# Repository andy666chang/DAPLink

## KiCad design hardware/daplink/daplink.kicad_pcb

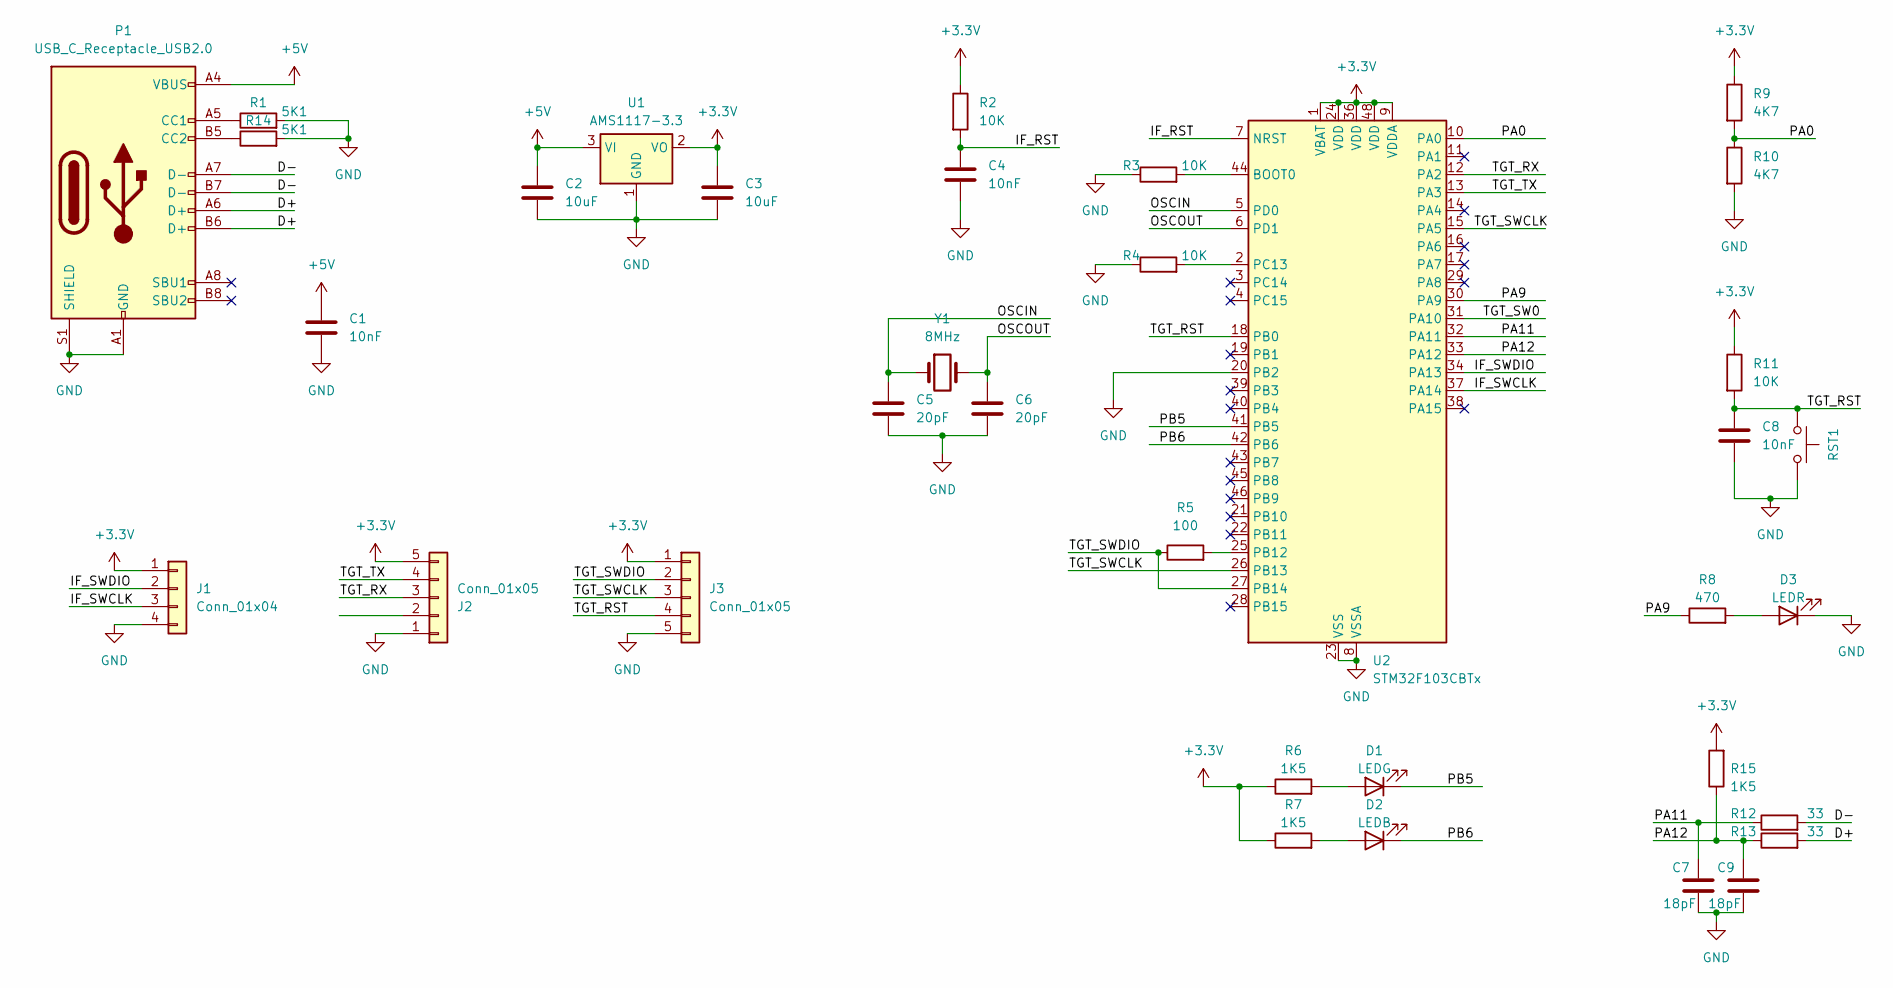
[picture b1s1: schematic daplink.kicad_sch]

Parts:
C1, C4, C8: 10nF; C_0603_1608Metric_Pad1.08x0.95mm_HandSolder; JLCPCB C57112
C2, C3: 10uF; C_0603_1608Metric_Pad1.08x0.95mm_HandSolder; JLCPCB C19702
C5, C6: 20pF; C_0603_1608Metric_Pad1.08x0.95mm_HandSolder; JLCPCB C1648
C7, C9: 18pF; C_0603_1608Metric_Pad1.08x0.95mm_HandSolder; JLCPCB C1647
D1: LEDG; LED_0603_1608Metric_Pad1.05x0.95mm_HandSolder; JLCPCB C72041
D2: LEDB; LED_0603_1608Metric_Pad1.05x0.95mm_HandSolder; JLCPCB C72043
D3: LEDR; LED_0603_1608Metric_Pad1.05x0.95mm_HandSolder; JLCPCB C2286
J1: Conn_01x04; PinHeader_1x04_P2.54mm_Vertical
J2, J3: Conn_01x05; Harwin_M20-89005xx_1x05_P2.54mm_Horizontal
P1: USB_C_Receptacle_USB2.0; USB_C_Receptacle_GCT_USB4105-xx-A_16P_TopMnt_Horizontal; JLCPCB C2927038/C2927029
R1, R14: 5K1; R_0603_1608Metric_Pad0.98x0.95mm_HandSolder; JLCPCB C25804
R2, R3, R4, R11: 10K; R_0603_1608Metric_Pad0.98x0.95mm_HandSolder; JLCPCB C25804
R5: 100; R_0603_1608Metric_Pad0.98x0.95mm_HandSolder; JLCPCB C23162
R6, R7, R15: 1K5; R_0603_1608Metric_Pad0.98x0.95mm_HandSolder; JLCPCB C22843
R8: 470; R_0603_1608Metric_Pad0.98x0.95mm_HandSolder; JLCPCB C23179
R9, R10: 4K7; R_0603_1608Metric_Pad0.98x0.95mm_HandSolder; JLCPCB C23162
R12, R13: 33; R_0603_1608Metric_Pad0.98x0.95mm_HandSolder; JLCPCB C23140
RST1: RST; SW_Push_SPST_NO_Alps_SKRK
U1: AMS1117-3.3; SOT-223-3_TabPin2; JLCPCB C6186
U2: STM32F103CBTx; LQFP-48_7x7mm_P0.5mm; JLCPCB C8304
Y1: 8MHz; Crystal_SMD_5032-2Pin_5.0x3.2mm; JLCPCB C115962

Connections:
+3.3V: C3.1, J1.1, J2.5, J3.1, R2.1, R6.1, R7.1, R9.1, R11.1, R15.2, U1.2 (VO), U2.1 (VBAT), U2.9 (VDDA), U2.24 (VDD), U2.36 (VDD), U2.48 (VDD)
+5V: C1.1, C2.1, P1.A4 (VBUS), P1.A9 (VBUS), P1.B4 (VBUS), P1.B9 (VBUS), U1.3 (VI)
/D+: P1.A6 (D+), P1.B6 (D+), R13.2
/D-: P1.A7 (D-), P1.B7 (D-), R12.2
/IF_RST: C4.1, R2.2, U2.7 (NRST)
/IF_SWCLK: J1.3, U2.37 (PA14)
/IF_SWDIO: J1.2, U2.34 (PA13)
/OSCIN: C5.1, U2.5 (PD0), Y1.1
/OSCOUT: C6.1, U2.6 (PD1), Y1.2
/PA0: R9.2, R10.1, U2.10 (PA0)
/PA9: R8.1, U2.30 (PA9)
/PA11: C7.1, R12.1, U2.32 (PA11)
/PA12: C9.1, R13.1, R15.1, U2.33 (PA12)
/PB5: D1.1 (K), U2.41 (PB5)
/PB6: D2.1 (K), U2.42 (PB6)
/TGT_RST: C8.1, J3.4, R11.2, RST1.1, U2.18 (PB0)
/TGT_RX: J2.3, U2.12 (PA2)
/TGT_SW0: U2.31 (PA10)
/TGT_SWCLK: J3.3, U2.15 (PA5), U2.26 (PB13)
/TGT_SWDIO: J3.2, R5.1, U2.27 (PB14)
/TGT_TX: J2.4, U2.13 (PA3)
GND: C1.2, C2.2, C3.2, C4.2, C5.2, C6.2, C7.2, C8.2, C9.2, D3.1 (K), J1.4, J2.1, J3.5, P1.A1 (GND), P1.A12 (GND), P1.B1 (GND), P1.B12 (GND), P1.S1 (SHIELD), R1.2, R3.1, R4.1, R10.2, R14.2, RST1.2, U1.1 (GND), U2.8 (VSSA), U2.20 (PB2), U2.23 (VSS), U2.35 (VSS), U2.47 (VSS)
unnamed: D1.2 (A), R6.2
unnamed: D2.2 (A), R7.2
unnamed: D3.2 (A), R8.2
unnamed: P1.A5 (CC1), R1.1
unnamed: P1.B5 (CC2), R14.1
unnamed: R3.2, U2.44 (BOOT0)
unnamed: R5.2, U2.25 (PB12)
unnamed: R4.2, U2.2 (PC13)

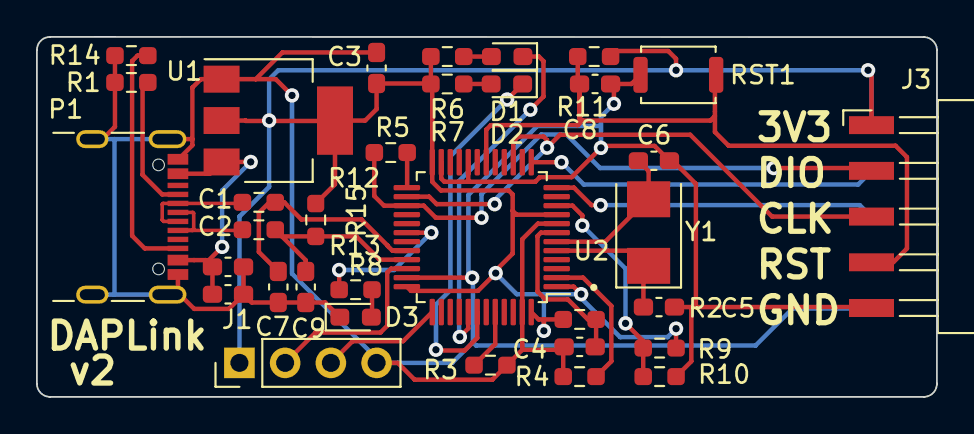
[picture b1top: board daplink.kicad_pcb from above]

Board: 2 copper layers, 50.0 x 20.0 mm, 35 parts (1 on the bottom side), 29 nets.

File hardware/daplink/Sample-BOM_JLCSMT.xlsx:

Comment | Designator | Footprint | JLCPCB Part #（optional）
10nF | C1 | Capacitor_SMD:C_0603_1608Metric_Pad1.08x0.95mm_HandSolder | C57112
10uF | C2 | Capacitor_SMD:C_0603_1608Metric_Pad1.08x0.95mm_HandSolder | C19702
10uF | C3 | Capacitor_SMD:C_0603_1608Metric_Pad1.08x0.95mm_HandSolder | C19702
10nF | C4 | Capacitor_SMD:C_0603_1608Metric_Pad1.08x0.95mm_HandSolder | C57112
20pF | C5 | Capacitor_SMD:C_0603_1608Metric_Pad1.08x0.95mm_HandSolder | C1648
20pF | C6 | Capacitor_SMD:C_0603_1608Metric_Pad1.08x0.95mm_HandSolder | C1648
18pF | C7 | Capacitor_SMD:C_0603_1608Metric_Pad1.08x0.95mm_HandSolder | C1647
10nF | C8 | Capacitor_SMD:C_0603_1608Metric_Pad1.08x0.95mm_HandSolder | C57112
18pF | C9 | Capacitor_SMD:C_0603_1608Metric_Pad1.08x0.95mm_HandSolder | C1647
LEDB | D1 | LED_SMD:LED_0603_1608Metric_Pad1.05x0.95mm_HandSolder | C72041
LEDG | D2 | LED_SMD:LED_0603_1608Metric_Pad1.05x0.95mm_HandSolder | C72043
LEDR | D3 | LED_SMD:LED_0603_1608Metric_Pad1.05x0.95mm_HandSolder | C2286
Conn_01x04 | J1 | Connector_PinHeader_2.54mm:PinHeader_1x04_P2.54mm_Vertical
Conn_01x05 | J2 | Connector_Harwin:Harwin_M20-89005xx_1x05_P2.54mm_Horizontal
Conn_01x05 | J3 | Connector_Harwin:Harwin_M20-89005xx_1x05_P2.54mm_Horizontal
USB_C_Plug_USB2.0 | P1 | Connector_USB:USB_C_Receptacle_GCT_USB4105-xx-A_16P_TopMnt_Horizontal | C2927038/C2927029
10K | R1 | Resistor_SMD:R_0603_1608Metric_Pad0.98x0.95mm_HandSolder | C25804
10K | R2 | Resistor_SMD:R_0603_1608Metric_Pad0.98x0.95mm_HandSolder | C25804
10K | R3 | Resistor_SMD:R_0603_1608Metric_Pad0.98x0.95mm_HandSolder | C25804
10K | R4 | Resistor_SMD:R_0603_1608Metric_Pad0.98x0.95mm_HandSolder | C25804
100 | R5 | Resistor_SMD:R_0603_1608Metric_Pad0.98x0.95mm_HandSolder | C22775
1K5 | R6 | Resistor_SMD:R_0603_1608Metric_Pad0.98x0.95mm_HandSolder | C22843
1K5 | R7 | Resistor_SMD:R_0603_1608Metric_Pad0.98x0.95mm_HandSolder | C22843
470 | R8 | Resistor_SMD:R_0603_1608Metric_Pad0.98x0.95mm_HandSolder | C23179
4K7 | R9 | Resistor_SMD:R_0603_1608Metric_Pad0.98x0.95mm_HandSolder | C23162
4K7 | R10 | Resistor_SMD:R_0603_1608Metric_Pad0.98x0.95mm_HandSolder | C23162
10K | R11 | Resistor_SMD:R_0603_1608Metric_Pad0.98x0.95mm_HandSolder | C25804
33 | R12 | Resistor_SMD:R_0603_1608Metric_Pad0.98x0.95mm_HandSolder | C23140
33 | R13 | Resistor_SMD:R_0603_1608Metric_Pad0.98x0.95mm_HandSolder | C23140
RST | RST1 | Button_Switch_SMD:SW_Push_SPST_NO_Alps_SKRK
AMS1117-3.3 | U1 | Package_TO_SOT_SMD:SOT-223-3_TabPin2 | C6186
STM32F103CBTx | U2 | Package_QFP:LQFP-48_7x7mm_P0.5mm | C8304
8MHz | Y1 | Crystal:Crystal_SMD_5032-2Pin_5.0x3.2mm | C115962

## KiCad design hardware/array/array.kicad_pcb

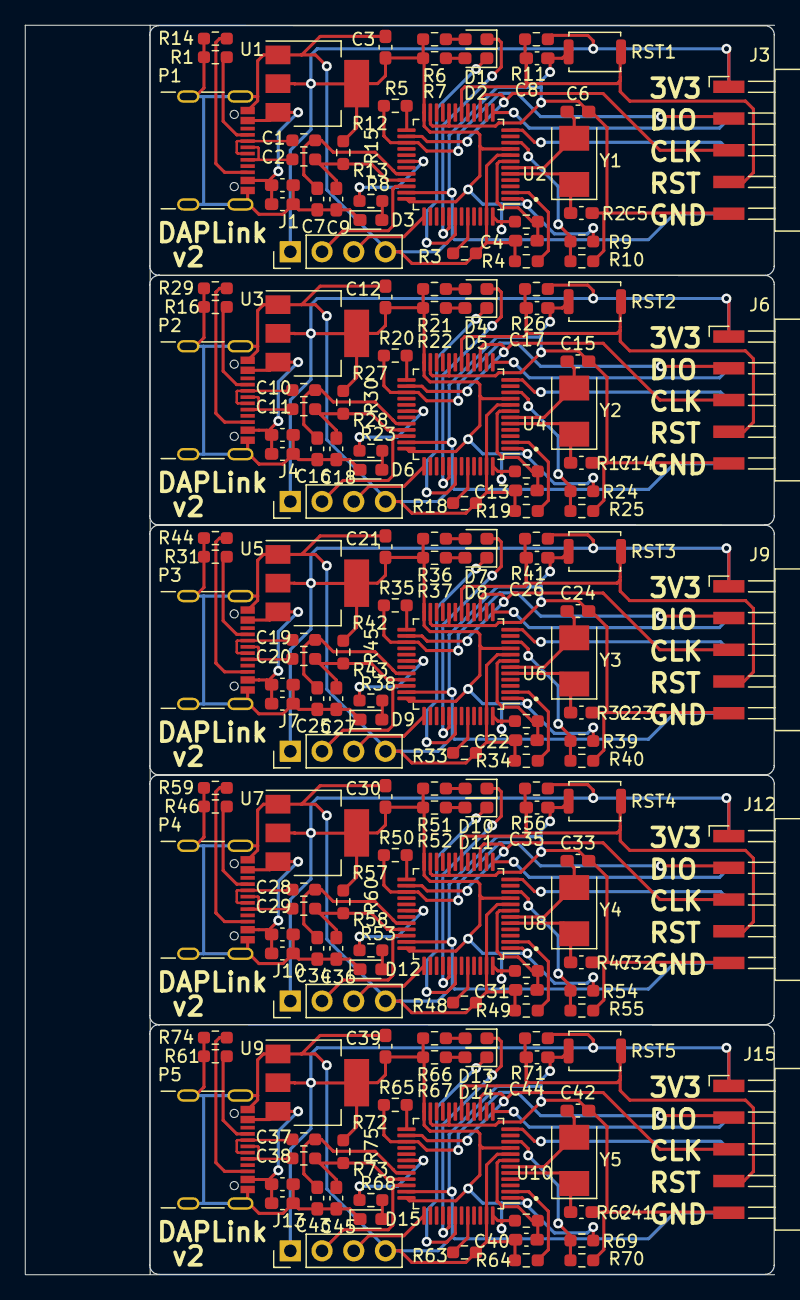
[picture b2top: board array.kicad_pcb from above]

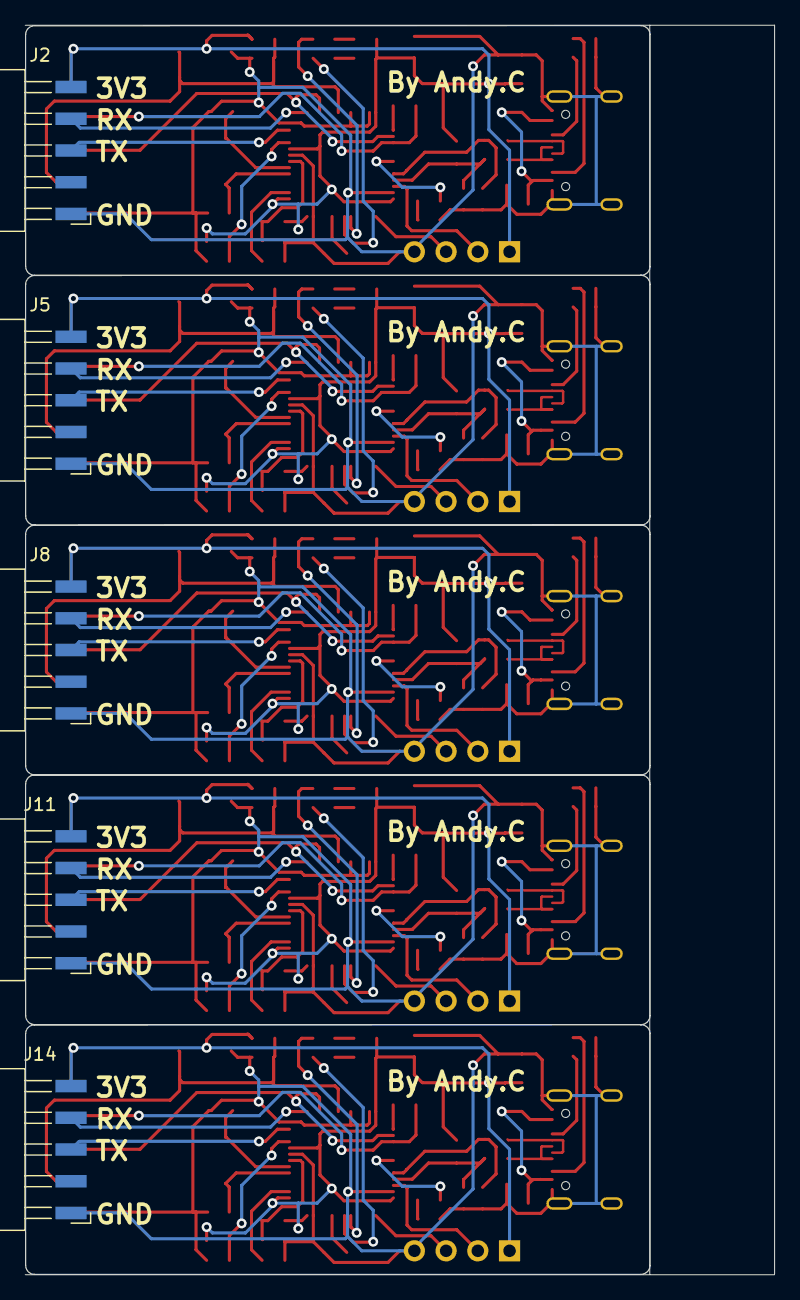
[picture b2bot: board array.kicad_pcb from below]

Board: 2 copper layers, 60.0 x 100.0 mm, 175 parts (5 on the bottom side), 30 nets.

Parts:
C1, C4, C8, C10, C13, C17, C19, C22, C26, C28, C31, C35, C37, C40, C44: 10nF; C_0603_1608Metric_Pad1.08x0.95mm_HandSolder
C2, C3, C11, C12, C20, C21, C29, C30, C38, C39: 10uF; C_0603_1608Metric_Pad1.08x0.95mm_HandSolder
C5, C6, C14, C15, C23, C24, C32, C33, C41, C42: 20pF; C_0603_1608Metric_Pad1.08x0.95mm_HandSolder
C7, C9, C16, C18, C25, C27, C34, C36, C43, C45: 18pF; C_0603_1608Metric_Pad1.08x0.95mm_HandSolder
D1, D4, D7, D10, D13: LEDG; LED_0603_1608Metric_Pad1.05x0.95mm_HandSolder
D2, D5, D8, D11, D14: LEDB; LED_0603_1608Metric_Pad1.05x0.95mm_HandSolder
D3, D6, D9, D12, D15: LEDR; LED_0603_1608Metric_Pad1.05x0.95mm_HandSolder
J1, J4, J7, J10, J13: Conn_01x04; PinHeader_1x04_P2.54mm_Vertical
J2, J3, J5, J6, J8, J9, J11, J12, J14, J15: Conn_01x05; Harwin_M20-89005xx_1x05_P2.54mm_Horizontal
P1, P2, P3, P4, P5: USB_C_Receptacle_USB2.0; USB_C_Receptacle_GCT_USB4105-xx-A_16P_TopMnt_Horizontal
R1, R14, R16, R29, R31, R44, R46, R59, R61, R74: 5K1; R_0603_1608Metric_Pad0.98x0.95mm_HandSolder
R2, R3, R4, R11, R17, R18, R19, R26, R32, R33, R34, R41, R47, R48, R49, R56, R62, R63, R64, R71: 10K; R_0603_1608Metric_Pad0.98x0.95mm_HandSolder
R5, R20, R35, R50, R65: 100; R_0603_1608Metric_Pad0.98x0.95mm_HandSolder
R6, R7, R15, R21, R22, R30, R36, R37, R45, R51, R52, R60, R66, R67, R75: 1K5; R_0603_1608Metric_Pad0.98x0.95mm_HandSolder
R8, R23, R38, R53, R68: 470; R_0603_1608Metric_Pad0.98x0.95mm_HandSolder
R9, R10, R24, R25, R39, R40, R54, R55, R69, R70: 4K7; R_0603_1608Metric_Pad0.98x0.95mm_HandSolder
R12, R13, R27, R28, R42, R43, R57, R58, R72, R73: 33; R_0603_1608Metric_Pad0.98x0.95mm_HandSolder
RST1, RST2, RST3, RST4, RST5: RST; SW_Push_SPST_NO_Alps_SKRK
U1, U3, U5, U7, U9: AMS1117-3.3; SOT-223-3_TabPin2
U2, U4, U6, U8, U10: STM32F103CBTx; LQFP-48_7x7mm_P0.5mm
Y1, Y2, Y3, Y4, Y5: 8MHz; Crystal_SMD_5032-2Pin_5.0x3.2mm

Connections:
+3.3V: C3.1, C12.1, C21.1, C30.1, C39.1, J1.1, J2.5, J3.1, J4.1, J5.5, J6.1, J7.1, J8.5, J9.1, J10.1, J11.5, J12.1, J13.1, J14.5, J15.1, R2.1, R6.1, R7.1, R9.1, R11.1, R15.2, R17.1, R21.1, R22.1, R24.1, R26.1, R30.2, R32.1, R36.1, R37.1, R39.1, R41.1, R45.2, R47.1, R51.1, R52.1, R54.1, R56.1, R60.2, R62.1, R66.1, R67.1, R69.1, R71.1, R75.2, U1.2 (VO), U2.1 (VBAT), U2.9 (VDDA), U2.24 (VDD), U2.36 (VDD), U2.48 (VDD), U3.2 (VO), U4.1 (VBAT), U4.9 (VDDA), U4.24 (VDD), U4.36 (VDD), U4.48 (VDD), U5.2 (VO), U6.1 (VBAT), U6.9 (VDDA), U6.24 (VDD), U6.36 (VDD), U6.48 (VDD), U7.2 (VO), U8.1 (VBAT), U8.9 (VDDA), U8.24 (VDD), U8.36 (VDD), U8.48 (VDD), U9.2 (VO), U10.1 (VBAT), U10.9 (VDDA), U10.24 (VDD), U10.36 (VDD), U10.48 (VDD)
+5V: C1.1, C2.1, C10.1, C11.1, C19.1, C20.1, C28.1, C29.1, C37.1, C38.1, P1.A4 (VBUS), P1.A9 (VBUS), P1.B4 (VBUS), P1.B9 (VBUS), P2.A4 (VBUS), P2.A9 (VBUS), P2.B4 (VBUS), P2.B9 (VBUS), P3.A4 (VBUS), P3.A9 (VBUS), P3.B4 (VBUS), P3.B9 (VBUS), P4.A4 (VBUS), P4.A9 (VBUS), P4.B4 (VBUS), P4.B9 (VBUS), P5.A4 (VBUS), P5.A9 (VBUS), P5.B4 (VBUS), P5.B9 (VBUS), U1.3 (VI), U3.3 (VI), U5.3 (VI), U7.3 (VI), U9.3 (VI)
/D+: P1.A6 (D+), P1.B6 (D+), P2.A6 (D+), P2.B6 (D+), P3.A6 (D+), P3.B6 (D+), P4.A6 (D+), P4.B6 (D+), P5.A6 (D+), P5.B6 (D+), R13.2, R28.2, R43.2, R58.2, R73.2
/D-: P1.A7 (D-), P1.B7 (D-), P2.A7 (D-), P2.B7 (D-), P3.A7 (D-), P3.B7 (D-), P4.A7 (D-), P4.B7 (D-), P5.A7 (D-), P5.B7 (D-), R12.2, R27.2, R42.2, R57.2, R72.2
/IF_RST: C4.1, C13.1, C22.1, C31.1, C40.1, R2.2, R17.2, R32.2, R47.2, R62.2, U2.7 (NRST), U4.7 (NRST), U6.7 (NRST), U8.7 (NRST), U10.7 (NRST)
/IF_SWCLK: J1.3, J4.3, J7.3, J10.3, J13.3, U2.37 (PA14), U4.37 (PA14), U6.37 (PA14), U8.37 (PA14), U10.37 (PA14)
/IF_SWDIO: J1.2, J4.2, J7.2, J10.2, J13.2, U2.34 (PA13), U4.34 (PA13), U6.34 (PA13), U8.34 (PA13), U10.34 (PA13)
/OSCIN: C5.1, C14.1, C23.1, C32.1, C41.1, U2.5 (PD0), U4.5 (PD0), U6.5 (PD0), U8.5 (PD0), U10.5 (PD0), Y1.1, Y2.1, Y3.1, Y4.1, Y5.1
/OSCOUT: C6.1, C15.1, C24.1, C33.1, C42.1, U2.6 (PD1), U4.6 (PD1), U6.6 (PD1), U8.6 (PD1), U10.6 (PD1), Y1.2, Y2.2, Y3.2, Y4.2, Y5.2
/PA0: R9.2, R10.1, R24.2, R25.1, R39.2, R40.1, R54.2, R55.1, R69.2, R70.1, U2.10 (PA0), U4.10 (PA0), U6.10 (PA0), U8.10 (PA0), U10.10 (PA0)
/PA9: R8.1, R23.1, R38.1, R53.1, R68.1, U2.30 (PA9), U4.30 (PA9), U6.30 (PA9), U8.30 (PA9), U10.30 (PA9)
/PA11: C7.1, C16.1, C25.1, C34.1, C43.1, R12.1, R27.1, R42.1, R57.1, R72.1, U2.32 (PA11), U4.32 (PA11), U6.32 (PA11), U8.32 (PA11), U10.32 (PA11)
/PA12: C9.1, C18.1, C27.1, C36.1, C45.1, R13.1, R15.1, R28.1, R30.1, R43.1, R45.1, R58.1, R60.1, R73.1, R75.1, U2.33 (PA12), U4.33 (PA12), U6.33 (PA12), U8.33 (PA12), U10.33 (PA12)
/PB5: D1.1 (K), D4.1 (K), D7.1 (K), D10.1 (K), D13.1 (K), U2.41 (PB5), U4.41 (PB5), U6.41 (PB5), U8.41 (PB5), U10.41 (PB5)
/PB6: D2.1 (K), D5.1 (K), D8.1 (K), D11.1 (K), D14.1 (K), U2.42 (PB6), U4.42 (PB6), U6.42 (PB6), U8.42 (PB6), U10.42 (PB6)
/TGT_RST: C8.1, C17.1, C26.1, C35.1, C44.1, J3.4, J6.4, J9.4, J12.4, J15.4, R11.2, R26.2, R41.2, R56.2, R71.2, RST1.1, RST2.1, RST3.1, RST4.1, RST5.1, U2.18 (PB0), U4.18 (PB0), U6.18 (PB0), U8.18 (PB0), U10.18 (PB0)
/TGT_RX: J2.3, J5.3, J8.3, J11.3, J14.3, U2.12 (PA2), U4.12 (PA2), U6.12 (PA2), U8.12 (PA2), U10.12 (PA2)
/TGT_SW0: U2.31 (PA10), U4.31 (PA10), U6.31 (PA10), U8.31 (PA10), U10.31 (PA10)
/TGT_SWCLK: J3.3, J6.3, J9.3, J12.3, J15.3, U2.15 (PA5), U2.26 (PB13), U4.15 (PA5), U4.26 (PB13), U6.15 (PA5), U6.26 (PB13), U8.15 (PA5), U8.26 (PB13), U10.15 (PA5), U10.26 (PB13)
/TGT_SWDIO: J3.2, J6.2, J9.2, J12.2, J15.2, R5.1, R20.1, R35.1, R50.1, R65.1, U2.27 (PB14), U4.27 (PB14), U6.27 (PB14), U8.27 (PB14), U10.27 (PB14)
/TGT_TX: J2.4, J5.4, J8.4, J11.4, J14.4, U2.13 (PA3), U4.13 (PA3), U6.13 (PA3), U8.13 (PA3), U10.13 (PA3)
GND: C1.2, C2.2, C3.2, C4.2, C5.2, C6.2, C7.2, C8.2, C9.2, C10.2, C11.2, C12.2, C13.2, C14.2, C15.2, C16.2, C17.2, C18.2, C19.2, C20.2, C21.2, C22.2, C23.2, C24.2, C25.2, C26.2, C27.2, C28.2, C29.2, C30.2, C31.2, C32.2, C33.2, C34.2, C35.2, C36.2, C37.2, C38.2, C39.2, C40.2, C41.2, C42.2, C43.2, C44.2, C45.2, D3.1 (K), D6.1 (K), D9.1 (K), D12.1 (K), D15.1 (K), J1.4, J2.1, J3.5, J4.4, J5.1, J6.5, J7.4, J8.1, J9.5, J10.4, J11.1, J12.5, J13.4, J14.1, J15.5, P1.A1 (GND), P1.A12 (GND), P1.B1 (GND), P1.B12 (GND), P1.S1 (SHIELD), P2.A1 (GND), P2.A12 (GND), P2.B1 (GND), P2.B12 (GND), P2.S1 (SHIELD), P3.A1 (GND), P3.A12 (GND), P3.B1 (GND), P3.B12 (GND), P3.S1 (SHIELD), P4.A1 (GND), P4.A12 (GND), P4.B1 (GND), P4.B12 (GND), P4.S1 (SHIELD), P5.A1 (GND), P5.A12 (GND), P5.B1 (GND), P5.B12 (GND), P5.S1 (SHIELD), R1.2, R3.1, R4.1, R10.2, R14.2, R16.2, R18.1, R19.1, R25.2, R29.2, R31.2, R33.1, R34.1, R40.2, R44.2, R46.2, R48.1, R49.1, R55.2, R59.2, R61.2, R63.1, R64.1, R70.2, R74.2, RST1.2, RST2.2, RST3.2, RST4.2, RST5.2, U1.1 (GND), U2.8 (VSSA), U2.20 (PB2), U2.23 (VSS), U2.35 (VSS), U2.47 (VSS), U3.1 (GND), U4.8 (VSSA), U4.20 (PB2), U4.23 (VSS), U4.35 (VSS), U4.47 (VSS), U5.1 (GND), U6.8 (VSSA), U6.20 (PB2), U6.23 (VSS), U6.35 (VSS), U6.47 (VSS), U7.1 (GND), U8.8 (VSSA), U8.20 (PB2), U8.23 (VSS), U8.35 (VSS), U8.47 (VSS), U9.1 (GND), U10.8 (VSSA), U10.20 (PB2), U10.23 (VSS), U10.35 (VSS), U10.47 (VSS)
unnamed: D1.2 (A), D4.2 (A), D7.2 (A), D10.2 (A), D13.2 (A), R6.2, R21.2, R36.2, R51.2, R66.2
unnamed: D2.2 (A), D5.2 (A), D8.2 (A), D11.2 (A), D14.2 (A), R7.2, R22.2, R37.2, R52.2, R67.2
unnamed: D3.2 (A), D6.2 (A), D9.2 (A), D12.2 (A), D15.2 (A), R8.2, R23.2, R38.2, R53.2, R68.2
unnamed: P1.A5 (CC1), P2.A5 (CC1), P3.A5 (CC1), P4.A5 (CC1), P5.A5 (CC1), R1.1, R16.1, R31.1, R46.1, R61.1
unnamed: P1.B5 (CC2), P2.B5 (CC2), P3.B5 (CC2), P4.B5 (CC2), P5.B5 (CC2), R14.1, R29.1, R44.1, R59.1, R74.1
unnamed: R3.2, R18.2, R33.2, R48.2, R63.2, U2.44 (BOOT0), U4.44 (BOOT0), U6.44 (BOOT0), U8.44 (BOOT0), U10.44 (BOOT0)
unnamed: R5.2, R20.2, R35.2, R50.2, R65.2, U2.25 (PB12), U4.25 (PB12), U6.25 (PB12), U8.25 (PB12), U10.25 (PB12)
unnamed: R4.2, R19.2, R34.2, R49.2, R64.2, U2.2 (PC13), U4.2 (PC13), U6.2 (PC13), U8.2 (PC13), U10.2 (PC13)

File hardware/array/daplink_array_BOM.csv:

"Reference","Value","Footprint","Datasheet","JLCPCB","數量"
"C1","10nF","Capacitor_SMD:C_0603_1608Metric_Pad1.08x0.95mm_HandSolder","~","C57112","1"
"C2","10uF","Capacitor_SMD:C_0603_1608Metric_Pad1.08x0.95mm_HandSolder","~","C19702","1"
"C3","10uF","Capacitor_SMD:C_0603_1608Metric_Pad1.08x0.95mm_HandSolder","~","C19702","1"
"C4","10nF","Capacitor_SMD:C_0603_1608Metric_Pad1.08x0.95mm_HandSolder","~","C57112","1"
"C5","20pF","Capacitor_SMD:C_0603_1608Metric_Pad1.08x0.95mm_HandSolder","~","C1648","1"
"C6","20pF","Capacitor_SMD:C_0603_1608Metric_Pad1.08x0.95mm_HandSolder","~","C1648","1"
"C7","18pF","Capacitor_SMD:C_0603_1608Metric_Pad1.08x0.95mm_HandSolder","~","C1647","1"
"C8","10nF","Capacitor_SMD:C_0603_1608Metric_Pad1.08x0.95mm_HandSolder","~","C57112","1"
"C9","18pF","Capacitor_SMD:C_0603_1608Metric_Pad1.08x0.95mm_HandSolder","~","C1647","1"
"D1","LEDG","LED_SMD:LED_0603_1608Metric_Pad1.05x0.95mm_HandSolder","~","C72041","1"
"D2","LEDB","LED_SMD:LED_0603_1608Metric_Pad1.05x0.95mm_HandSolder","~","C72043","1"
"D3","LEDR","LED_SMD:LED_0603_1608Metric_Pad1.05x0.95mm_HandSolder","~","C2286","1"
"J1","Conn_01x04","Connector_PinHeader_2.54mm:PinHeader_1x04_P2.54mm_Vertical","~","","1"
"J2","Conn_01x05","Connector_Harwin:Harwin_M20-89005xx_1x05_P2.54mm_Horizontal","~","","1"
"J3","Conn_01x05","Connector_Harwin:Harwin_M20-89005xx_1x05_P2.54mm_Horizontal","~","","1"
"P1","USB_C_Receptacle_USB2.0","Connector_USB:USB_C_Receptacle_GCT_USB4105-xx-A_16P_TopMnt_Horizontal","https://www.usb.org/sites/default/files/documents/usb_type-c.zip","C2927038/C2927029","1"
"R1","5K1","Resistor_SMD:R_0603_1608Metric_Pad0.98x0.95mm_HandSolder","~","C23186","1"
"R2","10K","Resistor_SMD:R_0603_1608Metric_Pad0.98x0.95mm_HandSolder","~","C25804","1"
"R3","10K","Resistor_SMD:R_0603_1608Metric_Pad0.98x0.95mm_HandSolder","~","C25804","1"
"R4","10K","Resistor_SMD:R_0603_1608Metric_Pad0.98x0.95mm_HandSolder","~","C25804","1"
"R5","100","Resistor_SMD:R_0603_1608Metric_Pad0.98x0.95mm_HandSolder","~","C22775","1"
"R6","1K5","Resistor_SMD:R_0603_1608Metric_Pad0.98x0.95mm_HandSolder","~","C22843","1"
"R7","1K5","Resistor_SMD:R_0603_1608Metric_Pad0.98x0.95mm_HandSolder","~","C22843","1"
"R8","470","Resistor_SMD:R_0603_1608Metric_Pad0.98x0.95mm_HandSolder","~","C23179","1"
"R9","4K7","Resistor_SMD:R_0603_1608Metric_Pad0.98x0.95mm_HandSolder","~","C23162","1"
"R10","4K7","Resistor_SMD:R_0603_1608Metric_Pad0.98x0.95mm_HandSolder","~","C23162","1"
"R11","10K","Resistor_SMD:R_0603_1608Metric_Pad0.98x0.95mm_HandSolder","~","C25804","1"
"R12","33","Resistor_SMD:R_0603_1608Metric_Pad0.98x0.95mm_HandSolder","~","C23140","1"
"R13","33","Resistor_SMD:R_0603_1608Metric_Pad0.98x0.95mm_HandSolder","~","C23140","1"
"R14","5K1","Resistor_SMD:R_0603_1608Metric_Pad0.98x0.95mm_HandSolder","~","C23186","1"
"R15","1K5","Resistor_SMD:R_0603_1608Metric_Pad0.98x0.95mm_HandSolder","~","C22843","1"
"RST1","RST","Button_Switch_SMD:SW_Push_SPST_NO_Alps_SKRK","~","","1"
"U1","AMS1117-3.3","Package_TO_SOT_SMD:SOT-223-3_TabPin2","http://www.advanced-monolithic.com/pdf/ds1117.pdf","C6186","1"
"U2","STM32F103CBTx","Package_QFP:LQFP-48_7x7mm_P0.5mm","https://www.st.com/resource/en/datasheet/stm32f103cb.pdf","C8304","1"
"Y1","8MHz","Crystal:Crystal_SMD_5032-2Pin_5.0x3.2mm","~","C115962","1"

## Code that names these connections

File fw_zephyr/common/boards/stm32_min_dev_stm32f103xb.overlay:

/*
 * DAPLink HIC (hardware/daplink) on stm32_min_dev (blue), STM32F103CB
 *
 * Shared by app (interface) and bootloader.
 *
 * Pin map follows DAPLink source/hic_hal/stm32/stm32f103xb/IO_Config.h
 * and hardware/daplink/daplink.kicad_sch:
 *   PB13  TGT_SWCLK
 *   PB14  TGT_SWDIO (out)
 *   PB12  TGT_SWDIO (in, via 4K7)
 *   PB0   TGT_RST   (open drain)
 *   PA2   TGT_RX    (USART2 TX -> target RX)
 *   PA3   TGT_TX    (USART2 RX <- target TX)
 *   PA10  TGT_SWO   (USART1 RX, SWO UART capture)
 *   PB6   LED blue  (active low)  - IF: connected
 *   PB5   LED green (active low)  - IF: CDC activity, BL: MSC activity
 *   PA9   LED red   (active high) - IF: DAP activity
 *   PA12  USB D+ fixed 1K5 pull-up (R15), no USB connect pin
 *
 * Memory map (DAPLink source/hic_hal/stm32/stm32f103xb/daplink_addr.h):
 *   0x08000000  bootloader  47 KB
 *   0x0800C000  interface   79 KB
 *   0x0801FC00  config user 1 KB
 *   0x20004F00  cfgram      256 B, shared BL <-> IF, not initialized
 *
 * SPDX-License-Identifier: Apache-2.0
 */

/ {
	model = "DAPLink HIC (STM32F103CB)";

	aliases {
		/delete-property/ led0;
	};

	chosen {
		/delete-property/ zephyr,console;
		/delete-property/ zephyr,shell-uart;
		/delete-property/ zephyr,osdp-uart;
		daplink,target-uart = &usart2;
		daplink,swo-uart = &usart1;
	};

	/delete-node/ leds;

	leds {
		compatible = "gpio-leds";

		led_connected: led_connected {
			gpios = <&gpiob 6 GPIO_ACTIVE_LOW>;
			label = "LED_CONNECTED";
		};

		led_cdc: led_cdc {
			gpios = <&gpiob 5 GPIO_ACTIVE_LOW>;
			label = "LED_CDC";
		};

		/* DAPLink PIN_MSC_LED, shared with CDC as in IO_Config.h */
		led_msc: led_msc {
			gpios = <&gpiob 5 GPIO_ACTIVE_LOW>;
			label = "LED_MSC";
		};

		led_dap: led_dap {
			gpios = <&gpioa 9 GPIO_ACTIVE_HIGH>;
			label = "LED_DAP";
		};
	};

	/* DAPLink settings.c config_ram, kept across BL <-> IF resets */
	cfgram: memory@20004f00 {
		compatible = "zephyr,memory-region", "mmio-sram";
		reg = <0x20004f00 0x100>;
		zephyr,memory-region = "cfgram";
	};

	zephyr,user {
		swclk-gpios = <&gpiob 13 GPIO_ACTIVE_HIGH>;
		swdio-out-gpios = <&gpiob 14 GPIO_ACTIVE_HIGH>;
		swdio-in-gpios = <&gpiob 12 GPIO_PULL_UP>;
		nreset-gpios = <&gpiob 0 (GPIO_OPEN_DRAIN | GPIO_PULL_UP)>;
	};
};

/* DAPLink HIC uses STM32F103CB (128 KB), the base board describes a C8 */
&flash0 {
	reg = <0x08000000 DT_SIZE_K(128)>;

	partitions {
		compatible = "fixed-partitions";
		#address-cells = <1>;
		#size-cells = <1>;

		bl_partition: partition@0 {
			label = "bootloader";
			reg = <0x00000000 0x0000bc00>;
		};

		if_partition: partition@c000 {
			label = "interface";
			reg = <0x0000c000 0x00013c00>;
		};

		config_partition: partition@1fc00 {
			label = "config-user";
			reg = <0x0001fc00 0x00000400>;
		};
	};
};

/* Remaining RAM after cfgram */
&sram0 {
	reg = <0x20000000 0x4f00>;
};

/*
 * SWO UART capture, driven directly by src/swo_uart.c (CMSIS-Driver USART
 * for DAPLink SWO.c). Kept "disabled" so the Zephyr serial driver does not
 * claim it; only RX is used, PA9 (USART1 TX) is the red LED.
 */
&usart1 {
	pinctrl-0 = <&usart1_rx_pa10>;
	pinctrl-names = "default";
	status = "disabled";
};

/* Pins shared with the DAPLink hardware, release them */
&usart3 {
	status = "disabled";
};

&i2c1 {
	status = "disabled";
};

&i2c2 {
	status = "disabled";
};

&spi1 {
	status = "disabled";
};

&adc1 {
	status = "disabled";
};

&spi2 {
	status = "disabled";
};

&timers1 {
	status = "disabled";
};

&pwm1 {
	status = "disabled";
};

/* Target UART */
&usart2 {
	pinctrl-0 = <&usart2_tx_pa2 &usart2_rx_pa3>;
	pinctrl-names = "default";
	current-speed = <115200>;
	status = "okay";
};

&zephyr_udc0 {
	cdc_acm_uart0: cdc_acm_uart0 {
		compatible = "zephyr,cdc-acm-uart";
	};
};

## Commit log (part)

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2024-02-03 feat: add daplink as submodule
2024-02-03 feat(module/daplink): switch to v0257
2024-02-03 feat(fw/daplink): build daplink fw
2024-02-03 test(fw/daplink): add test fw(stm32f103c8t6) for flashing test
2024-02-03 feat(hw/schematic): schematic wiring
2024-02-03 refactor(hw/schematic): refine net naming
2024-02-03 feat(hw/schematic): placement and layout
2024-02-03 feat(hw/schematic): refine placement
2024-02-04 refactor(hw/schematic): refine routing
2024-02-04 feat(hw/schematic): change the footprint of crystal
2024-02-04 feat(hw/schematic): update jlcpcb lib
2024-02-04 feat(hw/pcb): signed
2024-02-04 feat(hw/pcb): release gerber
2024-02-05 fix(hw/sch): fix uart and usb connection
2024-02-05 fix(hw/layout): refine rounting
2024-02-06 feat(hw/pcb): release panelization gerber
2024-02-06 feat: pr template
2024-02-06 fix(hw/sch): fix led and R5
2024-02-21 fix(hw/usb): d+ pull up and support usb-c flip
2024-10-20 refactor(hw/usb): modify board outline
2024-10-20 fix(hw/usb): fix part number
2024-10-20 feat(hw/usb): create board array
2025-03-09 feat(jlink): upload jlinkOB fw
